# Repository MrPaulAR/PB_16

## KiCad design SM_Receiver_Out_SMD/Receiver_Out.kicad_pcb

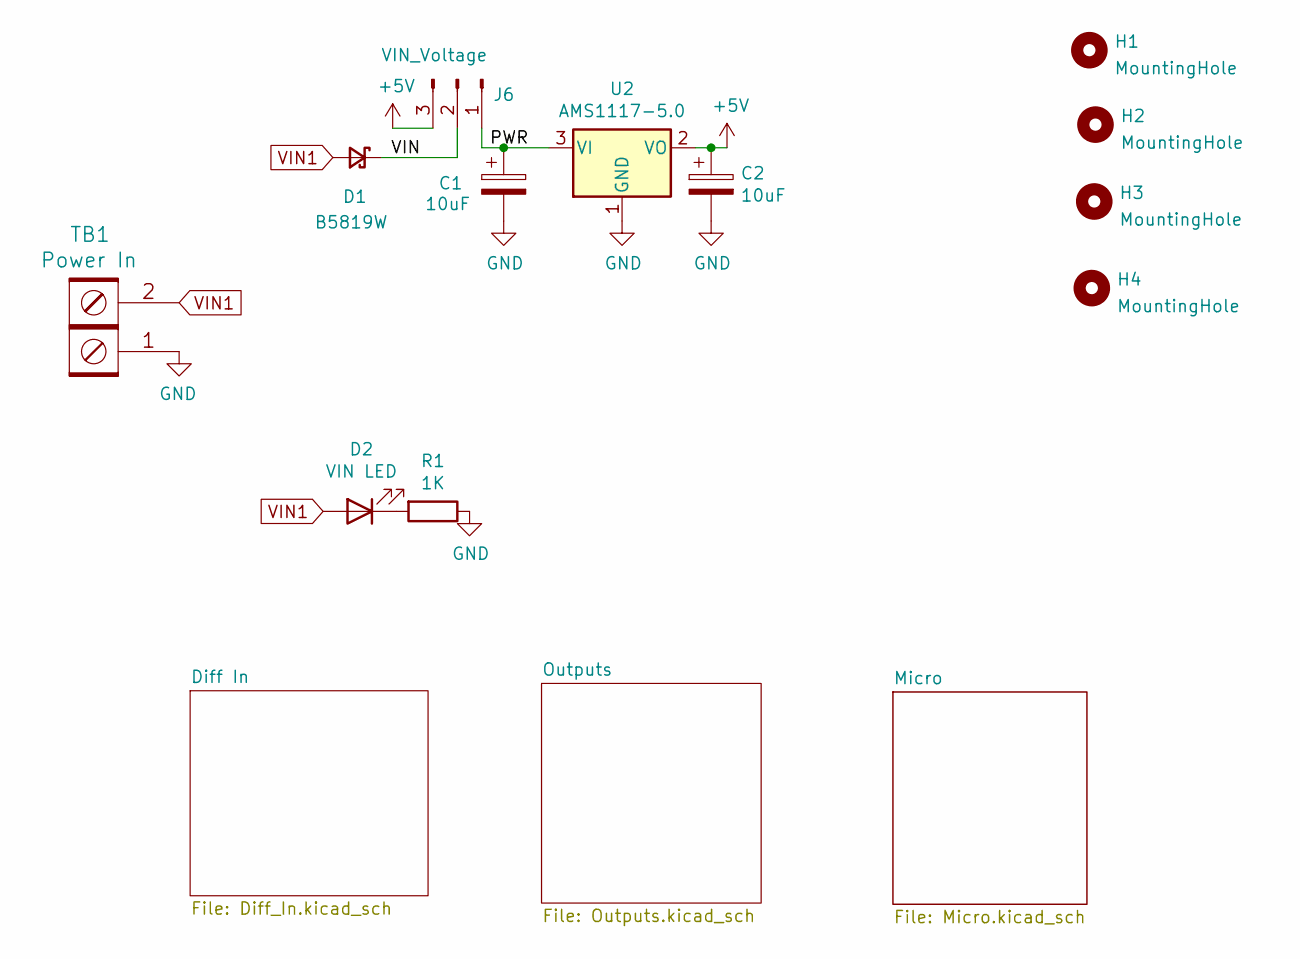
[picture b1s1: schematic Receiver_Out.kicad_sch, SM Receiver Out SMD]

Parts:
C1, C2: 10uF; C_0805_2012Metric_Pad1.18x1.45mm_HandSolder; MPN GRM21BR61E106KA73L; Digi-Key_PN 490-5523-1-ND
D1: B5819W; D_SOD-123; MPN B5819W-TP; LCSC_PN C8598
D2: VIN LED; LED_0603_1608Metric_Pad1.05x0.95mm_HandSolder; MPN 150080RS75000; Digi-Key_PN 732-4984-1-ND
H1, H2, H3, H4: MountingHole; MountingHole_3.7mm
J6: VIN_Voltage; PinHeader_1x03_P2.54mm_Vertical; MPN 61300311121; Digi-Key_PN 732-5316-ND
R1: 1K; R_0603_1608Metric_Pad0.98x0.95mm_HandSolder; MPN RC0603FR-071KL; Digi-Key_PN 311-1.00KHRCT-ND
TB1: Power In; BARRIER_BLOCK_1ROW_2POS; MPN 4DB-P108-02; Digi-Key_PN A98472-ND
U2: AMS1117-5.0; SOT-223-3_TabPin2; MPN LM1117MPX-50NOPB; LCSC_PN C6187

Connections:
+5V: C2.1, J6.3, U2.2 (VO); also elsewhere on the board
/PWR: C1.1, J6.1, U2.3 (VI)
/VIN: D1.1 (K), J6.2
GND: C1.2, C2.2, R1.1, TB1.1, U2.1 (GND); also elsewhere on the board
unnamed: D2.1 (K), R1.2
VIN1: D1.2 (A), D2.2 (A), TB1.2; also elsewhere on the board

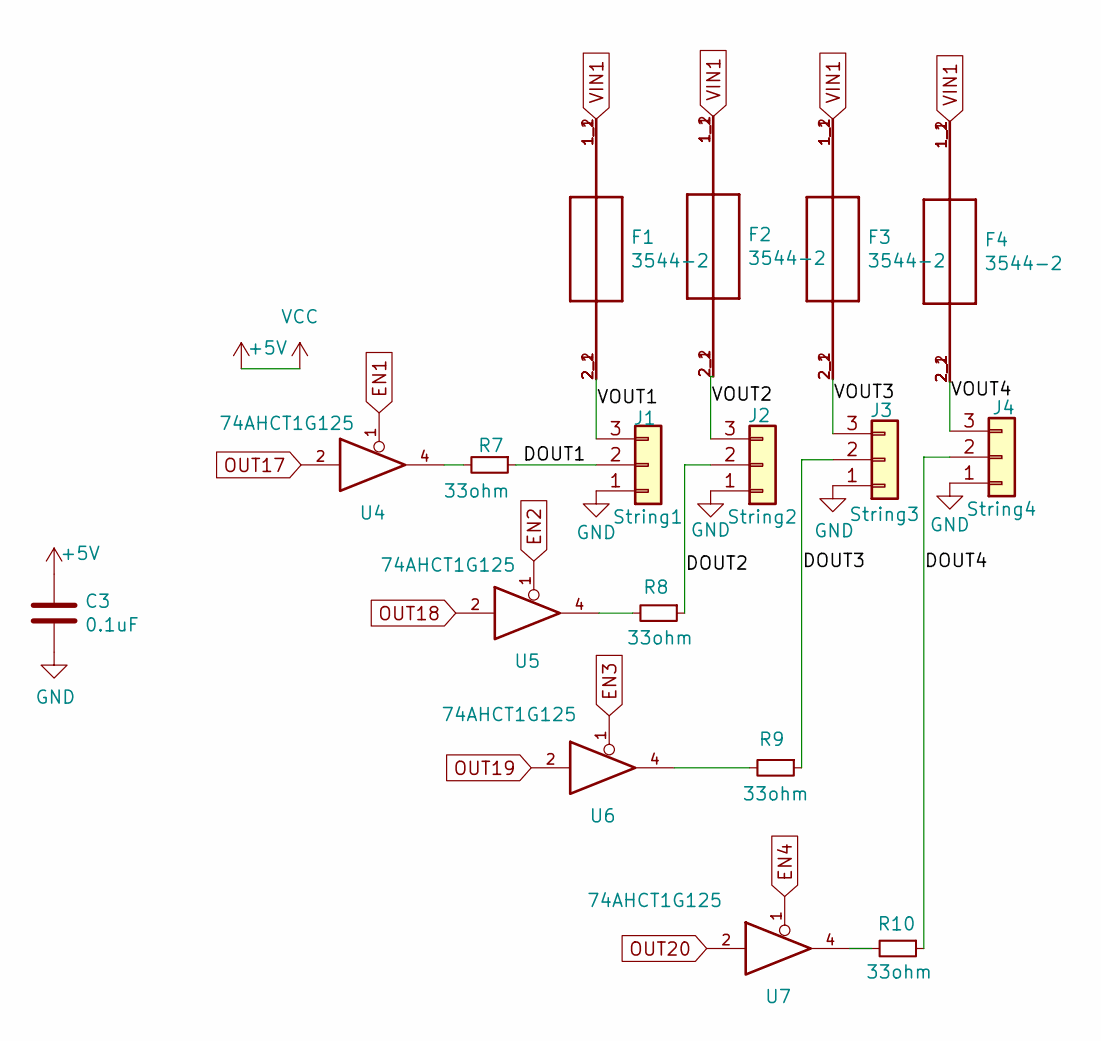
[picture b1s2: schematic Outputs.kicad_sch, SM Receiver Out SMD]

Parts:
C3: 0.1uF; C_0603_1608Metric_Pad1.08x0.95mm_HandSolder; MPN CL10B104KB8NNWC; Digi-Key_PN 1276-1935-2-ND
F1, F2, F3, F4: 3544-2; FUSE_3544-2; MPN 3544-2; Digi-Key_PN 36-3544-2-ND
J1: String1; PhoenixContact_MCV_1,5_3-G-3.5_1x03_P3.50mm_Vertical; MPN 1843619/OSTTJ0311530; Digi-Key_PN 277-5737-ND/ED10555-ND
J2: String2; PhoenixContact_MCV_1,5_3-G-3.5_1x03_P3.50mm_Vertical; MPN 1843619/OSTTJ0311530; Digi-Key_PN 277-5737-ND/ED10555-ND
J3: String3; PhoenixContact_MCV_1,5_3-G-3.5_1x03_P3.50mm_Vertical; MPN 1843619/OSTTJ0311530; Digi-Key_PN 277-5737-ND/ED10555-ND
J4: String4; PhoenixContact_MCV_1,5_3-G-3.5_1x03_P3.50mm_Vertical; MPN 1843619/OSTTJ0311530; Digi-Key_PN 277-5737-ND/ED10555-ND
R7, R8, R9, R10: 33ohm; R_0603_1608Metric_Pad0.98x0.95mm_HandSolder; MPN RC0603JR-0733RL; LCSC_PN C23140
U4, U5, U6, U7: 74AHCT1G125; TSOP-5_1.65x3.05mm_P0.95mm; MPN 74AHCT1G125W5-7; Digi-Key_PN 74AHCT1G125W5-7DICT-ND

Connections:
+5V: C3.1, U4.5 (VCC), U5.5 (VCC), U6.5 (VCC), U7.5 (VCC); also elsewhere on the board
/Outputs/DOUT1: J1.2, R7.1
/Outputs/DOUT2: J2.2, R8.1
/Outputs/DOUT3: J3.2, R9.1
/Outputs/DOUT4: J4.2, R10.1
/Outputs/VOUT1: F1.2_1 (2), F1.2_2 (2), J1.3
/Outputs/VOUT2: F2.2_1 (2), F2.2_2 (2), J2.3
/Outputs/VOUT3: F3.2_1 (2), F3.2_2 (2), J3.3
/Outputs/VOUT4: F4.2_1 (2), F4.2_2 (2), J4.3
EN1: U4.1; also elsewhere on the board
EN2: U5.1; also elsewhere on the board
EN3: U6.1; also elsewhere on the board
EN4: U7.1; also elsewhere on the board
GND: C3.2, J1.1, J2.1, J3.1, J4.1, U4.3 (GND), U5.3 (GND), U6.3 (GND), U7.3 (GND); also elsewhere on the board
unnamed: R7.2, U4.4
unnamed: R8.2, U5.4
unnamed: R9.2, U6.4
unnamed: R10.2, U7.4
OUT17: U4.2; also elsewhere on the board
OUT18: U5.2; also elsewhere on the board
OUT19: U6.2; also elsewhere on the board
OUT20: U7.2; also elsewhere on the board
VIN1: F1.1_1 (1), F1.1_2 (1), F2.1_1 (1), F2.1_2 (1), F3.1_1 (1), F3.1_2 (1), F4.1_1 (1), F4.1_2 (1); also elsewhere on the board

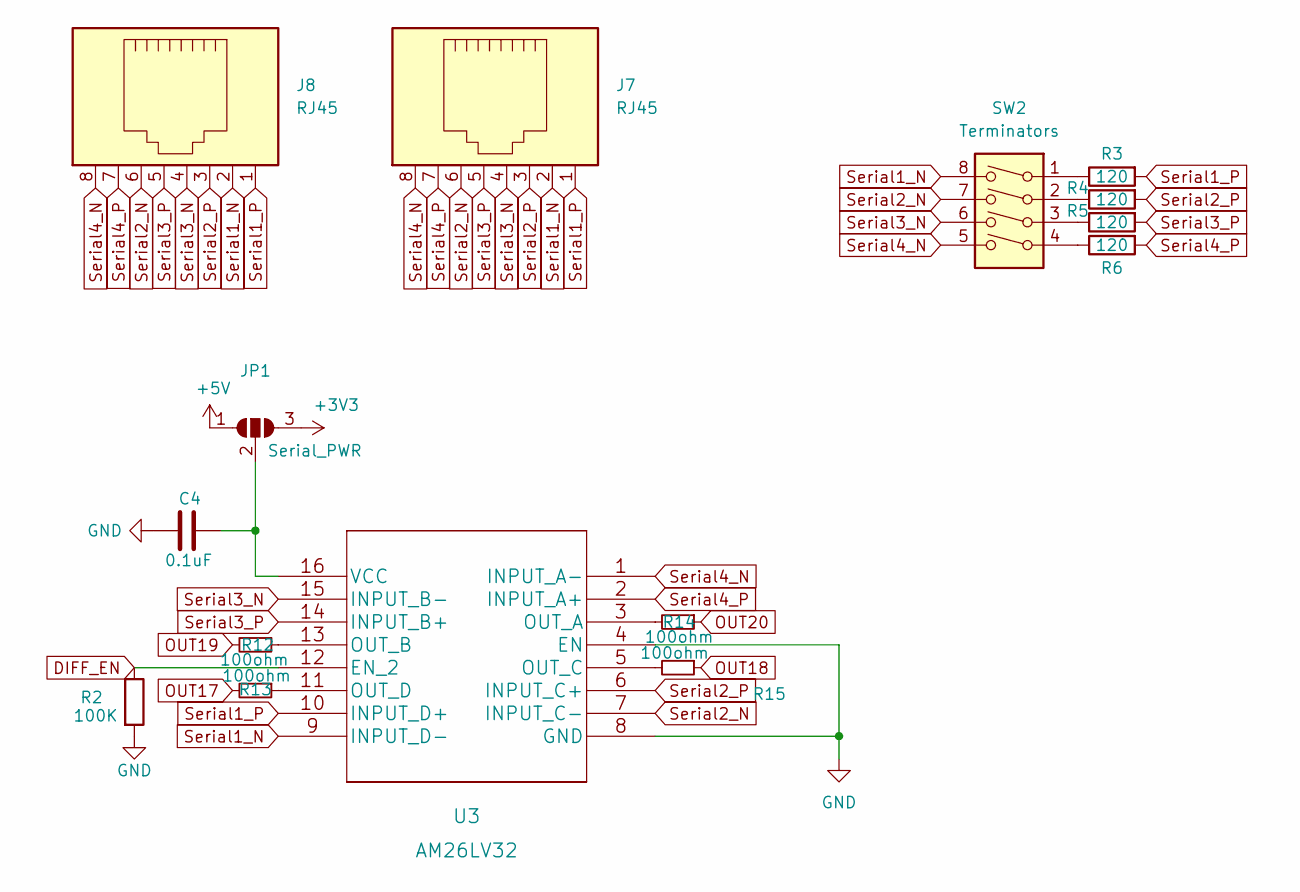
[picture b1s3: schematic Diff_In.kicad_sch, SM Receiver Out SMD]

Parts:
C4: 0.1uF; C_0603_1608Metric_Pad1.08x0.95mm_HandSolder; MPN CL10B104KB8NNWC; Digi-Key_PN 1276-1935-2-ND
J7, J8: RJ45; RJ45_Amphenol_54602-x08_Horizontal; MPN A-2014-2-4-R; Digi-Key_PN AE10392-ND
JP1: Serial_PWR; SolderJumper-3_P2.0mm_Open_TrianglePad1.0x1.5mm
R2: 100K; R_0603_1608Metric_Pad0.98x0.95mm_HandSolder; MPN RT0603BRD07100KL; Digi-Key_PN YAG1235CT-ND
R3, R4, R5, R6: 120; R_0603_1608Metric_Pad0.98x0.95mm_HandSolder; MPN CRGCQ0603F120R; LCSC_PN C22787
R12, R13: 100ohm; R_0603_1608Metric_Pad0.98x0.95mm_HandSolder; LCSC_PN C22775
R14, R15: 100ohm; R_0603_1608Metric_Pad0.98x0.95mm_HandSolder; MPN RC0603FR-07100RL; LCSC_PN C22775
SW2: Terminators; SW_DIP_SPSTx04_Slide_6.7x11.72mm_W7.62mm_P2.54mm_LowProfile; MPN DS04-254-1L-04BK; Digi-Key_PN 2223-DS04-254-1L-04BK-ND
U3: AM26LV32; SOIC-16_3.9x9.9mm_P1.27mm; MPN AM26LV32IDR; Digi-Key_PN 296-18090-1-ND

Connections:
+3V3: JP1.3 (B); also elsewhere on the board
+5V: JP1.1 (A); also elsewhere on the board
DIFF_EN: R2.1, U3.12 (EN_2); also elsewhere on the board
GND: C4.2, R2.2, U3.4 (EN), U3.8 (GND); also elsewhere on the board
unnamed: C4.1, JP1.2 (C), U3.16 (VCC)
unnamed: R3.1, SW2.1
unnamed: R4.1, SW2.2
unnamed: R5.1, SW2.3
unnamed: R6.1, SW2.4
unnamed: R14.2, U3.3 (OUT_A)
unnamed: R12.1, U3.13 (OUT_B)
unnamed: R15.2, U3.5 (OUT_C)
unnamed: R13.1, U3.11 (OUT_D)
OUT17: R13.2; also elsewhere on the board
OUT18: R15.1; also elsewhere on the board
OUT19: R12.2; also elsewhere on the board
OUT20: R14.1; also elsewhere on the board
Serial1_N: J7.2, J8.2, SW2.8, U3.9 (INPUT_D-)
Serial1_P: J7.1, J8.1, R3.2, U3.10 (INPUT_D+)
Serial2_N: J7.6, J8.6, SW2.7, U3.7 (INPUT_C-)
Serial2_P: J7.3, J8.3, R4.2, U3.6 (INPUT_C+)
Serial3_N: J7.4, J8.4, SW2.6, U3.15 (INPUT_B-)
Serial3_P: J7.5, J8.5, R5.2, U3.14 (INPUT_B+)
Serial4_N: J7.8, J8.8, SW2.5, U3.1 (INPUT_A-)
Serial4_P: J7.7, J8.7, R6.2, U3.2 (INPUT_A+)

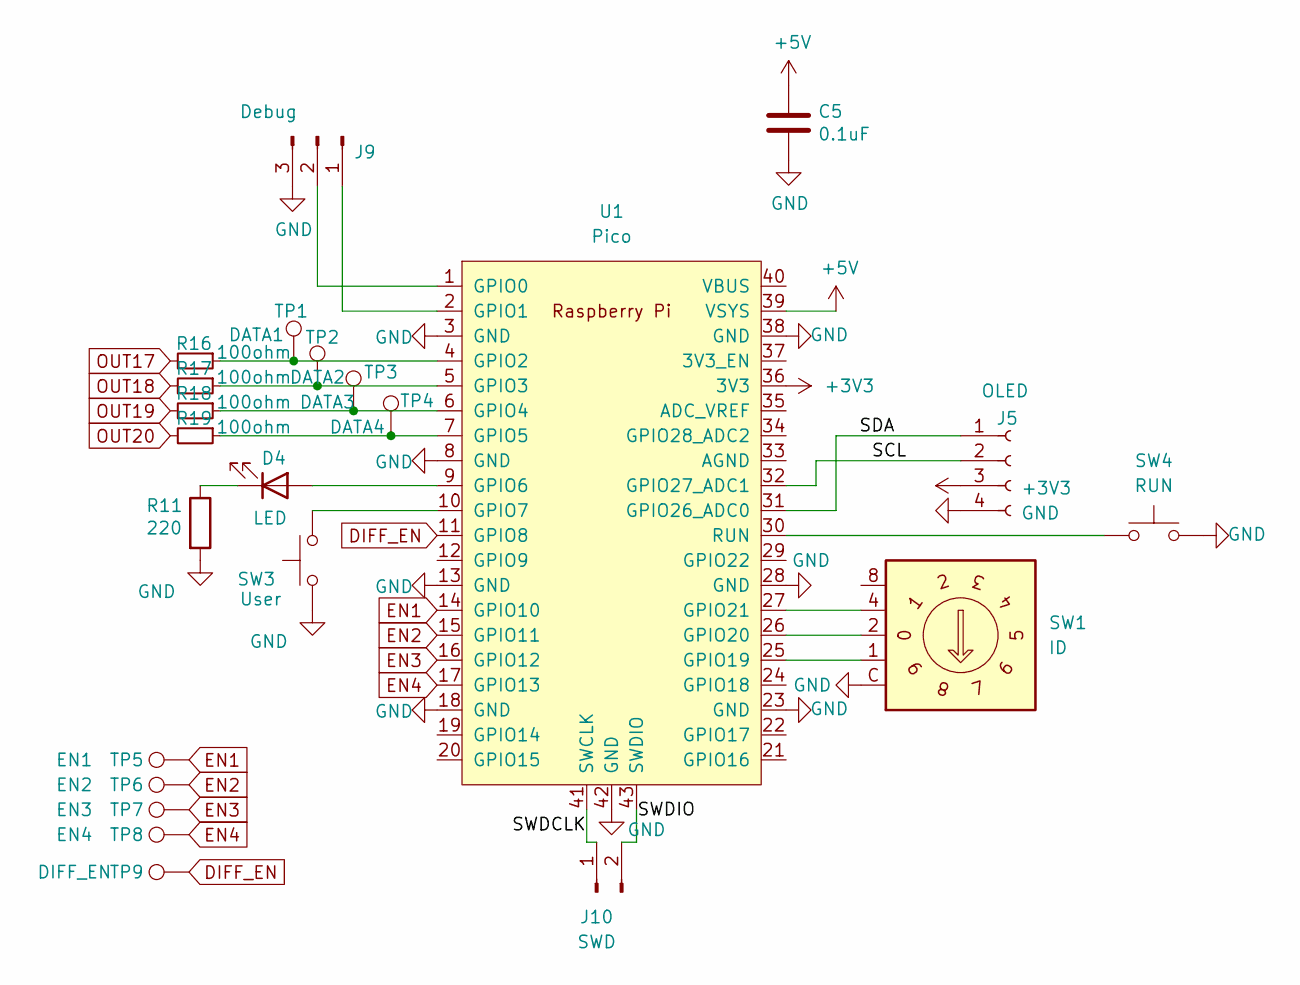
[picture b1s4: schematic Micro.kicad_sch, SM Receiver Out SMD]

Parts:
C5: 0.1uF; C_0603_1608Metric_Pad1.08x0.95mm_HandSolder; MPN CL10B104KB8NNWC; Digi-Key_PN 1276-1935-2-ND
D4: LED; LED_0603_1608Metric_Pad1.05x0.95mm_HandSolder; MPN 150080RS75000; Digi-Key_PN 732-4984-1-ND
J5: OLED; OLED-SSD1306-128X64-I2C-THT; MPN PPTC041LFBN-RC; Digi-Key_PN S7002-ND
J9: Debug; PinHeader_1x03_P2.54mm_Vertical; MPN 61300311121; Digi-Key_PN 732-5316-ND
J10: SWD; 1x02_Horizontal_SMD; MPN 61300211121; Digi-Key_PN 732-5315-ND
R11: 220; R_0603_1608Metric_Pad0.98x0.95mm_HandSolder; MPN RMCF0603FT220R; Digi-Key_PN RMCF0603FT220RTR-ND
R16, R17, R18, R19: 100ohm; R_0603_1608Metric_Pad0.98x0.95mm_HandSolder; MPN RC0603FR-07100RL; LCSC_PN C22775
SW1: ID; Nidec_Copal_SH-7010C; MPN SD-2010; Digi-Key_PN 563-1069-ND
SW3: User; SW_Push_1P1T_NO_6x6mm_H9.5mm; MPN PTS645SL50SMTR92 LFS; Digi-Key_PN CKN9088CT-ND
SW4: RUN; SW_Push_1P1T_NO_6x6mm_H9.5mm; MPN PTS645SL50SMTR92 LFS; Digi-Key_PN CKN9088CT-ND
TP1: DATA1; TestPoint_Pad_D1.5mm
TP2: DATA2; TestPoint_Pad_D1.5mm
TP3: DATA3; TestPoint_Pad_D1.5mm
TP4: DATA4; TestPoint_Pad_D1.5mm
TP5: EN1; TestPoint_Pad_D1.5mm
TP6: EN2; TestPoint_Pad_D1.5mm
TP7: EN3; TestPoint_Pad_D1.5mm
TP8: EN4; TestPoint_Pad_D1.5mm
TP9: DIFF_EN; TestPoint_Pad_D1.5mm
U1: Pico; RPi_Pico_SMD_TH; MPN 2648-SC0915CT-ND; Digi-Key_PN SC0915

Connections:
+3V3: J5.3, U1.36 (3V3); also elsewhere on the board
+5V: C5.1, U1.39 (VSYS); also elsewhere on the board
/Micro/SCL: J5.2, U1.32 (GPIO27_ADC1)
/Micro/SDA: J5.1, U1.31 (GPIO26_ADC0)
/Micro/SWDCLK: J10.1, U1.41 (SWCLK)
/Micro/SWDIO: J10.2, U1.43 (SWDIO)
DIFF_EN: TP9.1, U1.11 (GPIO8); also elsewhere on the board
EN1: TP5.1, U1.14 (GPIO10); also elsewhere on the board
EN2: TP6.1, U1.15 (GPIO11); also elsewhere on the board
EN3: TP7.1, U1.16 (GPIO12); also elsewhere on the board
EN4: TP8.1, U1.17 (GPIO13); also elsewhere on the board
GND: C5.2, J5.4, J9.3, R11.2, SW1.C, SW3.1, SW4.2, U1.3 (GND), U1.8 (GND), U1.13 (GND), U1.18 (GND), U1.23 (GND), U1.28 (GND), U1.38 (GND), U1.42 (GND); also elsewhere on the board
unnamed: D4.2 (A), U1.9 (GPIO6)
unnamed: D4.1 (K), R11.1
unnamed: J9.1, U1.2 (GPIO1)
unnamed: J9.2, U1.1 (GPIO0)
unnamed: R16.1, TP1.1, U1.4 (GPIO2)
unnamed: R17.1, TP2.1, U1.5 (GPIO3)
unnamed: R18.1, TP3.1, U1.6 (GPIO4)
unnamed: R19.1, TP4.1, U1.7 (GPIO5)
unnamed: SW3.2, U1.10 (GPIO7)
unnamed: SW1.1, U1.25 (GPIO19)
unnamed: SW1.2, U1.26 (GPIO20)
unnamed: SW1.4, U1.27 (GPIO21)
unnamed: SW4.1, U1.30 (RUN)
OUT17: R16.2; also elsewhere on the board
OUT18: R17.2; also elsewhere on the board
OUT19: R18.2; also elsewhere on the board
OUT20: R19.2; also elsewhere on the board

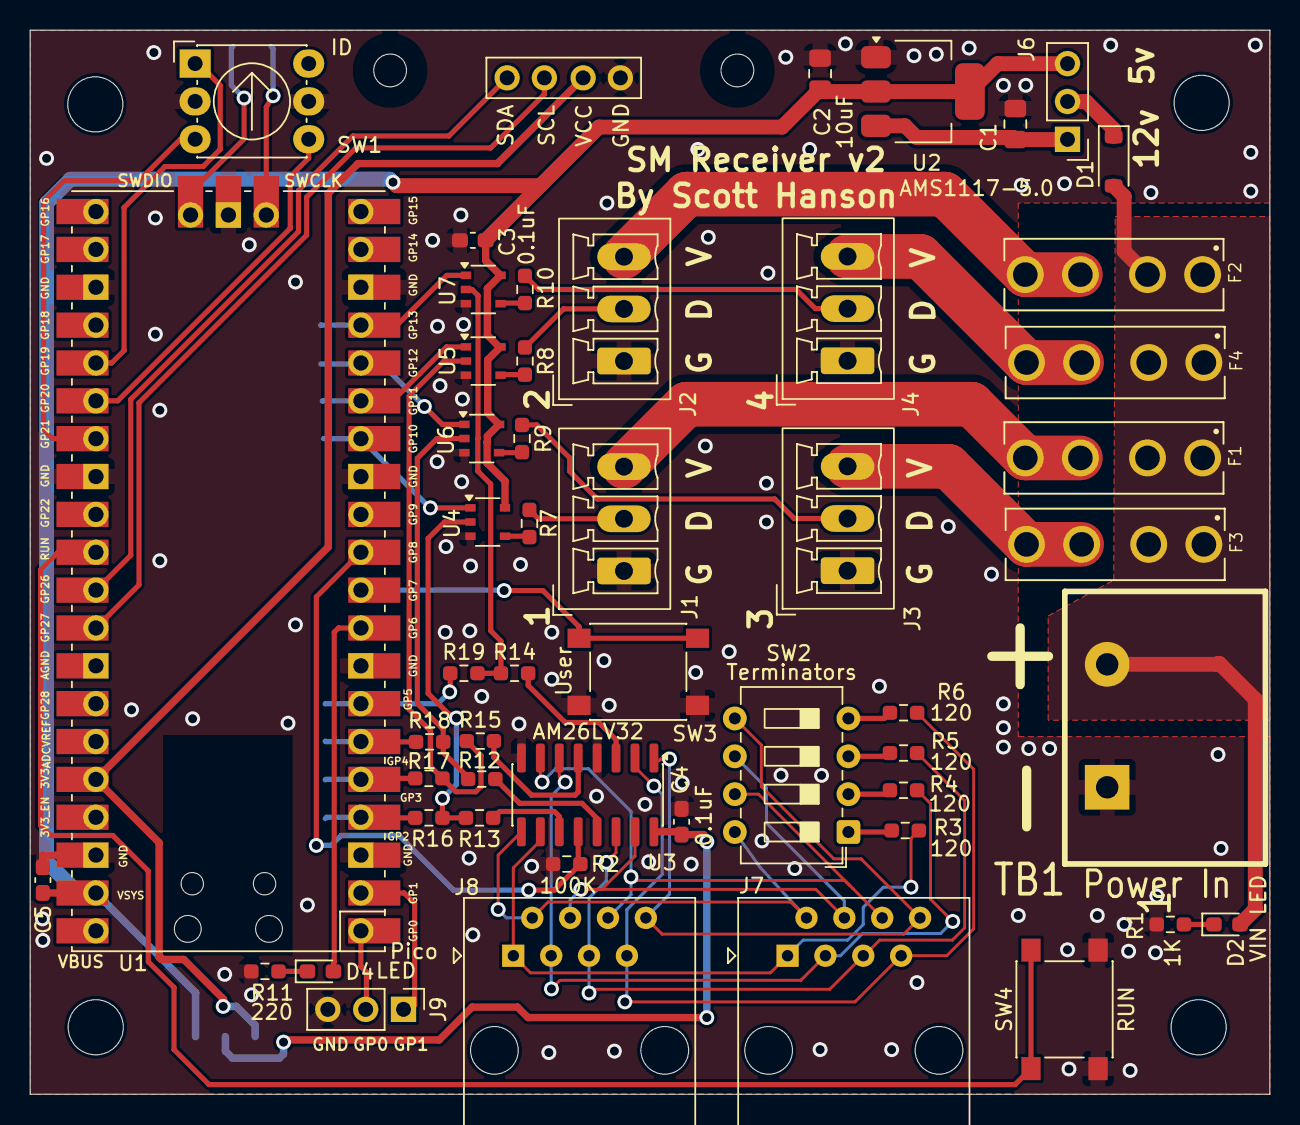
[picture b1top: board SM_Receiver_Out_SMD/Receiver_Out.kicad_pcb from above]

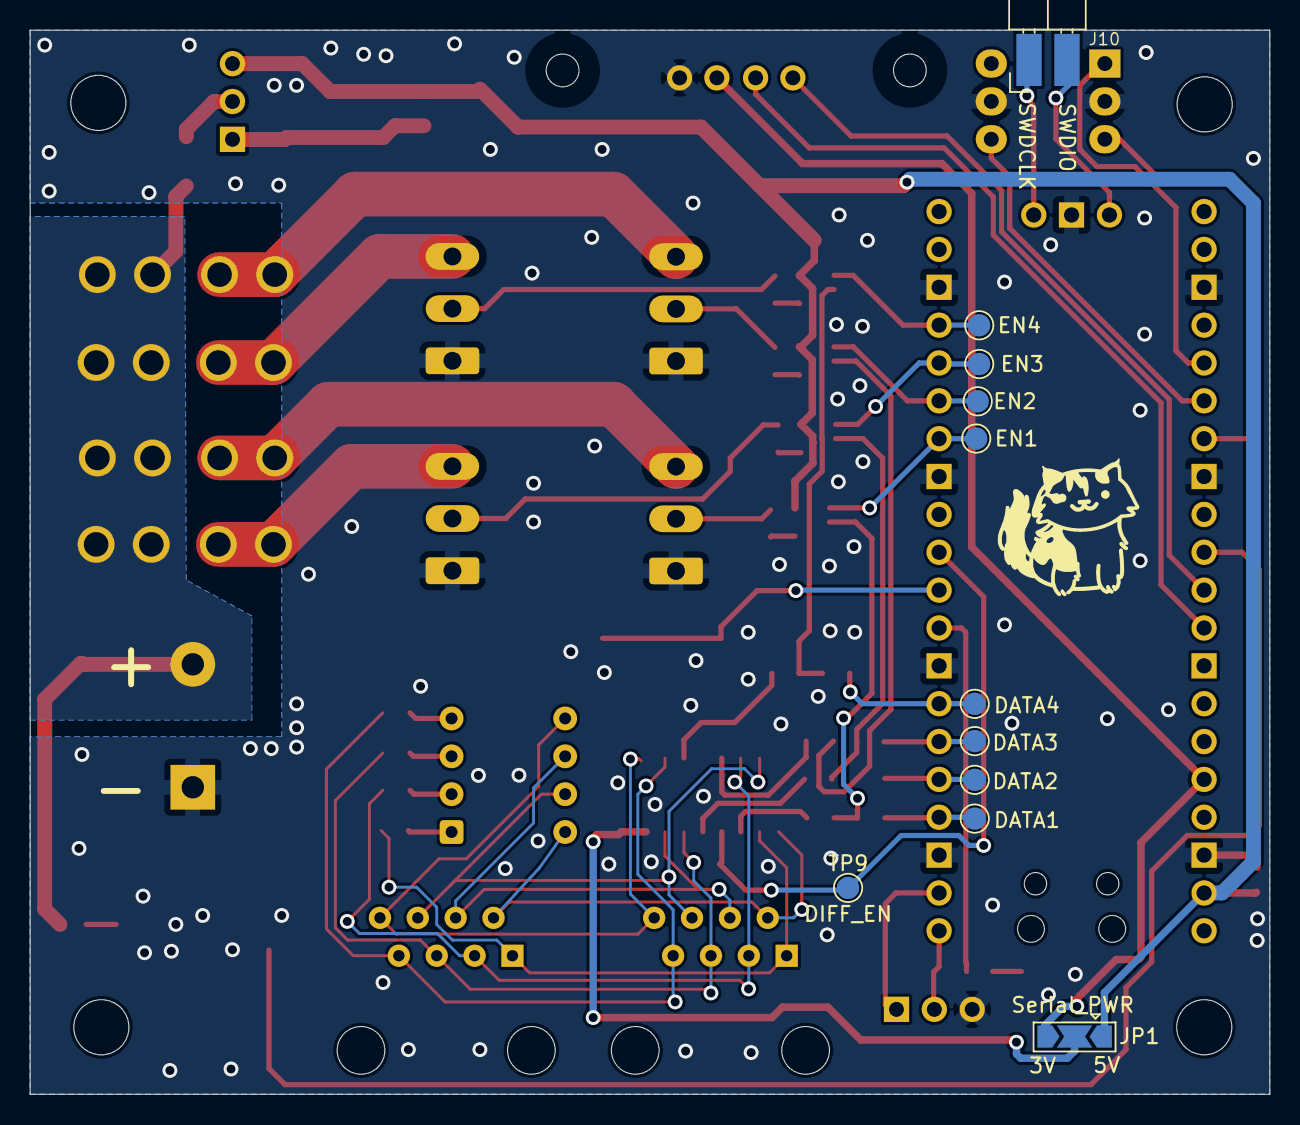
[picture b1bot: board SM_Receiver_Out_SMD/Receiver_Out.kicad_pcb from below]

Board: 2 copper layers, 83.2 x 71.4 mm, 67 parts (11 on the bottom side), 62 nets.

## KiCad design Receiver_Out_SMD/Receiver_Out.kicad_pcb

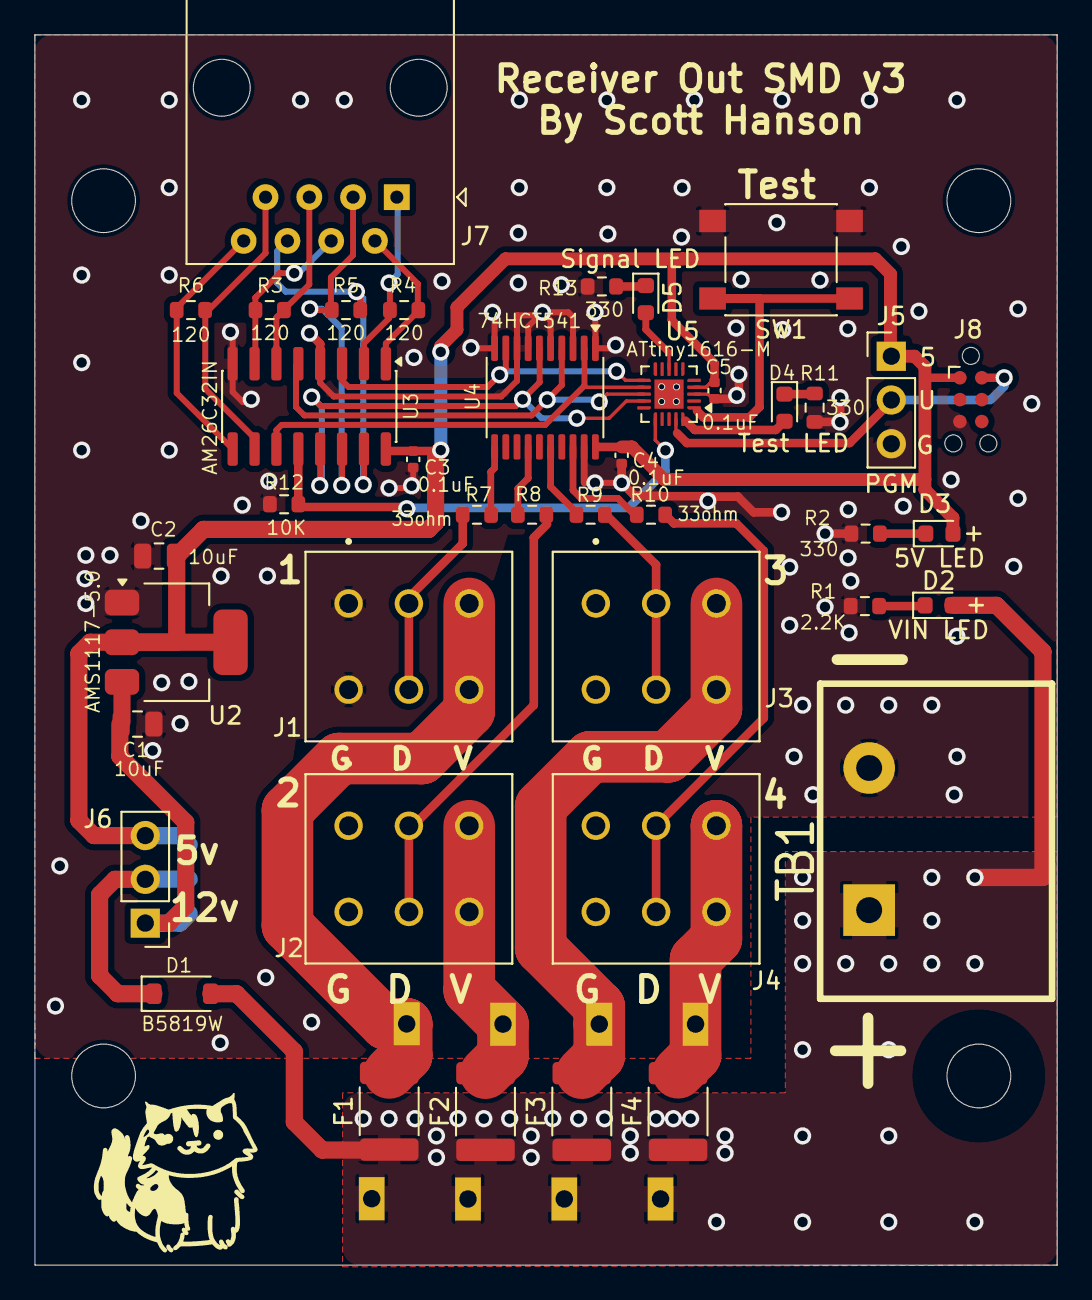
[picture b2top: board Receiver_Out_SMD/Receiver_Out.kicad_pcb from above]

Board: 2 copper layers, 59.3 x 71.4 mm, 46 parts (1 on the bottom side), 38 nets.

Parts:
C1, C2: 10uF; C_0805_2012Metric
C3, C4, C5: 0.1uF; C_0402_1005Metric
D1: B5819W; D_SOD-123
D2: VIN LED; LED_0603_1608Metric
D3: 5V LED; LED_0603_1608Metric
D4: Test LED; LED_0603_1608Metric
D5: Signal LED; LED_0603_1608Metric
F1, F2, F3, F4: 1812L400/16GR; Fuse_1812_4532Metric
H1, H2, H3, H4: MountingHole; MountingHole_3.7mm
J1: String1; PHOENIX_1864299
J2: String2; PHOENIX_1864299
J3: String3; PHOENIX_1864299
J4: String4; PHOENIX_1864299
J5: PGM; PinHeader_1x03_P2.54mm_Vertical
J6: VIN_Voltage; PinHeader_1x03_P2.54mm_Vertical
J7: RJ45; RJ45_Amphenol_54602-x08_Horizontal
J8: Conn_ARM_SWD_TagConnect_TC2030-NL; Tag-Connect_TC2030-IDC-NL_2x03_P1.27mm_Vertical
JP1: PWR_JMP; SolderJumper-3_P2.0mm_Open_TrianglePad1.0x1.5mm
R1: 2.2K; R_0603_1608Metric
R2, R11, R13: 330; R_0603_1608Metric
R3, R4, R5, R6: 120; R_0603_1608Metric
R7, R8, R9, R10: 33ohm; R_0603_1608Metric
R12: 10K; R_0603_1608Metric
SW1: Test; SW_Push_1P1T_NO_6x6mm_H9.5mm
TB1: Power In; BARRIER_BLOCK_1ROW_2POS
U2: AMS1117-5.0; SOT-223-3_TabPin2
U3: AM26C32IN; SOIC-16_3.9x9.9mm_P1.27mm
U4: 74HCT541; TSSOP-20_4.4x6.5mm_P0.65mm
U5: ATtiny1616-M; VQFN-20-1EP_3x3mm_P0.4mm_EP1.7x1.7mm

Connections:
+5V: C2.1, C3.1, C4.1, C5.1, D3.2 (A), J5.1, J6.3, J8.1 (VCC), JP1.1 (A), U2.2 (VO), U3.16 (VCC), U4.20 (VCC), U5.4 (VCC)
/Diff In/Serial1_N: J7.2, R4.1, U3.1 (INPUT_A-)
/Diff In/Serial1_P: J7.1, R4.2, U3.2 (INPUT_A+)
/Diff In/Serial2_N: J7.6, R5.2, U3.15 (INPUT_B-)
/Diff In/Serial2_P: J7.3, R5.1, U3.14 (INPUT_B+)
/Diff In/Serial3_N: J7.4, R3.2, U3.7 (INPUT_C-)
/Diff In/Serial3_P: J7.5, R3.1, U3.6 (INPUT_C+)
/Diff In/Serial4_N: J7.8, R6.1, U3.9 (INPUT_D-)
/Diff In/Serial4_P: J7.7, R6.2, U3.10 (INPUT_D+)
/Outputs/DOUT1: J1.2, R7.1
/Outputs/DOUT2: J2.2, R8.1
/Outputs/DOUT3: J3.2, R9.1
/Outputs/DOUT4: J4.2, R10.1
/Outputs/VOUT1: F1.2, J1.3
/Outputs/VOUT2: F2.2, J2.3
/Outputs/VOUT3: F3.2, J3.3
/Outputs/VOUT4: F4.2, J4.3
GND: C1.2, C2.2, C3.2, C4.2, C5.2, J1.1, J2.1, J3.1, J4.1, J5.3, J8.5 (GND), R1.1, R2.1, R11.1, R12.2, R13.1, SW1.2, TB1.2, U2.1 (GND), U3.4 (EN), U3.8 (GND), U4.1 (G1), U4.3 (A1), U4.5 (A3), U4.7 (A5), U4.8 (A6), U4.10 (GND), U4.19 (G2), U5.3 (GND), U5.21 (GND)
unnamed: D2.1 (K), R1.2
unnamed: D3.1 (K), R2.2
unnamed: D4.1 (K), R11.2
unnamed: D5.1 (K), R13.2
unnamed: R10.2, U4.18 (Y0)
unnamed: R9.2, U4.16 (Y2)
unnamed: R8.2, U4.14 (Y4)
unnamed: R7.2, U4.11 (Y7)
unnamed: SW1.1, U5.1 (PA2)
OUT17: U3.3 (OUT_A), U4.9 (A7), U5.11 (PB3)
OUT18: U3.13 (OUT_B), U4.6 (A4), U5.14 (PB0)
OUT19: U3.5 (OUT_C), U4.4 (A2), U5.13 (PB1)
OUT20: U3.11 (OUT_D), U4.2 (A0), U5.12 (PB2)
OUT_EN: R12.1, U3.12 (EN_2), U5.16 (PC1)
PWR: C1.1, J6.1, JP1.3 (B), U2.3 (VI)
SIGNLED: D5.2 (A), U5.8 (PA7)
TESTLED: D4.2 (A), U5.20 (PA1)
UPDI_DATA: J5.2, J8.2 (SWDIO), U5.19 (~RESET/PA0)
VIN: D1.1 (K), J6.2, JP1.2 (C)
VIN1: D1.2 (A), D2.2 (A), F1.1, F2.1, F3.1, F4.1, TB1.1

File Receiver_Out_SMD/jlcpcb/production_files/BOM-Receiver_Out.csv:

Comment,Designator,Footprint,LCSC,Quantity
0.1uF,"C3,C4,C5",C_0402_1005Metric,C1525,3
10K,R12,R_0603_1608Metric,C25804,1
10uF,"C1,C2",C_0805_2012Metric,C15850,2
120,"R3,R4,R5,R6",R_0603_1608Metric,C22787,4
1812L400/16GR,"F1,F2,F3,F4",Fuse_1812_4532Metric,C22374900,4
2.2K,R1,R_0603_1608Metric,C4190,1
330,"R11,R13,R2",R_0603_1608Metric,C23138,3
33ohm,"R10,R7,R8,R9",R_0603_1608Metric,C23140,4
5V LED,D3,LED_0603_1608Metric,C2286,1
74HCT541,U4,TSSOP-20_4.4x6.5mm_P0.65mm,C436096,1
AM26C32IN,U3,SOIC-16_3.9x9.9mm_P1.27mm,C6180,1
AMS1117-5.0,U2,SOT-223-3_TabPin2,C6187,1
ATtiny1616-M,U5,VQFN-20-1EP_3x3mm_P0.4mm_EP1.7x1.7mm,C507118,1
B5819W,D1,D_SOD-123,C8598,1
Power In,TB1,BARRIER_BLOCK_1ROW_2POS,C5188513,1
RJ45,J7,RJ45_Amphenol_54602-x08_Horizontal,C86492,1
Signal LED,D5,LED_0603_1608Metric,C2286,1
String1,J1,PHOENIX_1864299,C6394553,1
String2,J2,PHOENIX_1864299,C6394553,1
String3,J3,PHOENIX_1864299,C6394553,1
String4,J4,PHOENIX_1864299,C6394553,1
Test,SW1,SW_Push_1P1T_NO_6x6mm_H9.5mm,C255812,1
Test LED,D4,LED_0603_1608Metric,C2286,1
VIN LED,D2,LED_0603_1608Metric,C2286,1
VIN_Voltage,J6,PinHeader_1x03_P2.54mm_Vertical,C49257,1

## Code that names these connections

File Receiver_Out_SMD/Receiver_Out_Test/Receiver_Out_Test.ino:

#include <FAB_LED.h>
#include <OneButton.h>

const uint16_t numPixels = 300;

avrBitbangLedStrip<WS2812B_1H_CY, WS2812B_1L_CY, WS2812B_0H_CY, WS2812B_0L_CY,
                    WS2812B_MS_REFRESH, B, 3, A, 0, RGB, ONE_PORT_BITBANG> myLeds1;  // NeoPixel data on PB3
avrBitbangLedStrip<WS2812B_1H_CY, WS2812B_1L_CY, WS2812B_0H_CY, WS2812B_0L_CY,
                    WS2812B_MS_REFRESH, B, 0, A, 0, RGB, ONE_PORT_BITBANG> myLeds2;  // NeoPixel data on PB0
avrBitbangLedStrip<WS2812B_1H_CY, WS2812B_1L_CY, WS2812B_0H_CY, WS2812B_0L_CY,
                    WS2812B_MS_REFRESH, B, 1, A, 0, RGB, ONE_PORT_BITBANG> myLeds3;  // NeoPixel data on PB1
avrBitbangLedStrip<WS2812B_1H_CY, WS2812B_1L_CY, WS2812B_0H_CY, WS2812B_0L_CY,
                    WS2812B_MS_REFRESH, B, 2, A, 0, RGB, ONE_PORT_BITBANG> myLeds4;  // NeoPixel data on PB2

//ws2812b<B,3> myLeds1;
//ws2812b<B,0> myLeds2;
//ws2812b<B,1> myLeds3;
//ws2812b<B,2> myLeds4;
//ws2812b8s<B,0,7> strip_split8;//maybe?

volatile bool test_en = false;

volatile int mode = 0;

volatile unsigned long previousMillis = 0;

// constants won't change:
const long interval = 1000;

// --- WS2812 data detection on PB3, status LED on PA7 ---
const uint8_t DATA_PIN_BM = (1 << 3);    // PB3 bitmask within PORTB
const unsigned long dataTimeoutMs = 250; // consider data "lost" after this idle time
#define WS_DETECT_ISC PORT_ISC_RISING_gc // interrupt on rising edges (line idles low)
volatile bool wsActivity = false;        // set by the pin-change ISR on each edge
unsigned long lastDataMillis = 0;        // last time activity was seen on PB3
bool dataLedOn = false;                  // current state of the PA7 status LED

////////////////////////////////////////////////////////////////////////////////
/// @brief Pin-change ISR for PORTB.
/// The WS2812 line idles low and produces a rising edge for every bit clocked
/// in, so any edge means data is present. We only flag activity here; the loop
/// timestamps it. The PB3 interrupt is disabled while test mode drives PORTB.
////////////////////////////////////////////////////////////////////////////////
ISR(PORTB_PORT_vect)
{
  if (PORTB.INTFLAGS & DATA_PIN_BM)
  {
    PORTB.INTFLAGS = DATA_PIN_BM; // clear the flag (write 1 to clear)
    wsActivity = true;
  }
}

OneButton  button = OneButton (
  PIN_PA2,  // Input pin for the button
  true,        // Button is active LOW
  true         // Enable internal pull-up resistor
);

////////////////////////////////////////////////////////////////////////////////
/// @brief Display numPixels with one solid color.
/// We only use a 3 byte array, storing one pixel.
/// We then send the same pixel repeatedly to the LED strip very fast.
/// This demonstrates the ability tocall the library repeatedly.
/// If this feature fails, you may see only 1 pixel lit, or a varying number
/// of pixels glitching on and off.
////////////////////////////////////////////////////////////////////////////////
void color1N(uint8_t red, uint8_t green, uint8_t blue)
{
  rgb pix[1];

  pix[0].r = red;
  pix[0].g = green;
  pix[0].b = blue;

  // Disable interupts, save the old interupt state
  const uint8_t oldSREG = SREG;
  cli();

  // Display the LEDs. Each strip must be streamed contiguously: the gap
  // between successive sendPixels() calls on the SAME pin is only a few us,
  // well under the WS2812 latch time. Interleaving the four strips would
  // leave each line idle ~90us between its pixels, latching the strip after
  // the first pixel (symptom: only the first LED lights up).
  for (uint16_t i = 0; i < numPixels; i++) { myLeds1.sendPixels(1, pix); }
  for (uint16_t i = 0; i < numPixels; i++) { myLeds2.sendPixels(1, pix); }
  for (uint16_t i = 0; i < numPixels; i++) { myLeds3.sendPixels(1, pix); }
  for (uint16_t i = 0; i < numPixels; i++) { myLeds4.sendPixels(1, pix); }

  // Restore the old interrupt state
  SREG = oldSREG;
}

void LongPress(void * /*oneButton*/)
{
  if(test_en)
  {
    myLeds1.clear(numPixels);
    myLeds2.clear(numPixels);
    myLeds3.clear(numPixels);
    myLeds4.clear(numPixels);
    digitalWrite(PIN_PA1, LOW);
    //FAB_PORT(B, 0x00); // all pins low
    PORTB.DIR =    0b00000000;
    PORTB.PIN0CTRL = 0;
    PORTB.PIN1CTRL = 0;
    PORTB.PIN2CTRL = 0;
    PORTB.PIN3CTRL = WS_DETECT_ISC; // re-enable WS2812 data-detect interrupt on PB3
    digitalWrite(PIN_PC1, LOW);
  }
  else
  {
    digitalWrite(PIN_PC1, HIGH);
    digitalWrite(PIN_PA1, HIGH);
    FAB_PORT(B, 0x00); // all pins low
    FAB_DDR(B, 0xFF); // all pins out
    PORTB.PIN3CTRL = 0; // disable PB3 interrupt while test mode drives PORTB
    myLeds1.clear(numPixels);
    myLeds2.clear(numPixels);
    myLeds3.clear(numPixels);
    myLeds4.clear(numPixels);
    previousMillis = 0;
  }
  test_en = !test_en;
}

////////////////////////////////////////////////////////////////////////////////
/// @brief This method is automatically called once when the board boots.
////////////////////////////////////////////////////////////////////////////////
void setup()
{
  pinMode(PIN_PC1, OUTPUT);
  pinMode(PIN_PA1, OUTPUT);
  pinMode(PIN_PA7, OUTPUT);     // WS2812 data-present status LED
  digitalWrite(PIN_PA7, LOW);
  //digitalWrite(PIN_PC1, HIGH);

  // button.attachPress(ShortPress, &button);
  button.attachLongPressStart(LongPress, &button);
  button.setDebounceMs(20);
  button.setLongPressIntervalMs(1000);

  //FAB_PORT(B, 0x00); // all pins low
  PORTB.DIR = 0b00000000;
  PORTB.PIN0CTRL = 0;
  PORTB.PIN1CTRL = 0;
  PORTB.PIN2CTRL = 0;
  PORTB.PIN3CTRL = WS_DETECT_ISC; // enable WS2812 data-detect interrupt on PB3
  digitalWrite(PIN_PC1, LOW);
  digitalWrite(PIN_PA1, LOW);
}

void loop()
{
  button.tick();
  unsigned long currentMillis = millis();
  if (currentMillis - previousMillis >= interval)
  {
    previousMillis = currentMillis;
    if(test_en)
    {
      switch(mode) {
        case 0:
          color1N(127,0,0);
          mode = 1;
          break;
        case 1:
          color1N(0,127,0);
          mode = 2;
          break;
        case 2:
          color1N(0,0,127);
          mode = 0;
          break;
      }
    }
  }

  // WS2812 data detection (PB3) -> status LED (PA7).
  // Only valid while test mode is off, since test mode drives PORTB as outputs.
  if (!test_en)
  {
    // Atomically read & clear the activity flag set by the pin-change ISR.
    uint8_t oldSREG = SREG;
    cli();
    bool act = wsActivity;
    wsActivity = false;
    SREG = oldSREG;

    if (act)
    {
      lastDataMillis = currentMillis;
    }
    bool present = (currentMillis - lastDataMillis) < dataTimeoutMs;
    if (present != dataLedOn)
    {
      dataLedOn = present;
      digitalWrite(PIN_PA7, present ? HIGH : LOW);
    }
  }
  else if (dataLedOn)
  {
    // Entered test mode: turn the data-present LED off.
    dataLedOn = false;
    digitalWrite(PIN_PA7, LOW);
  }

  delay(10);
}
